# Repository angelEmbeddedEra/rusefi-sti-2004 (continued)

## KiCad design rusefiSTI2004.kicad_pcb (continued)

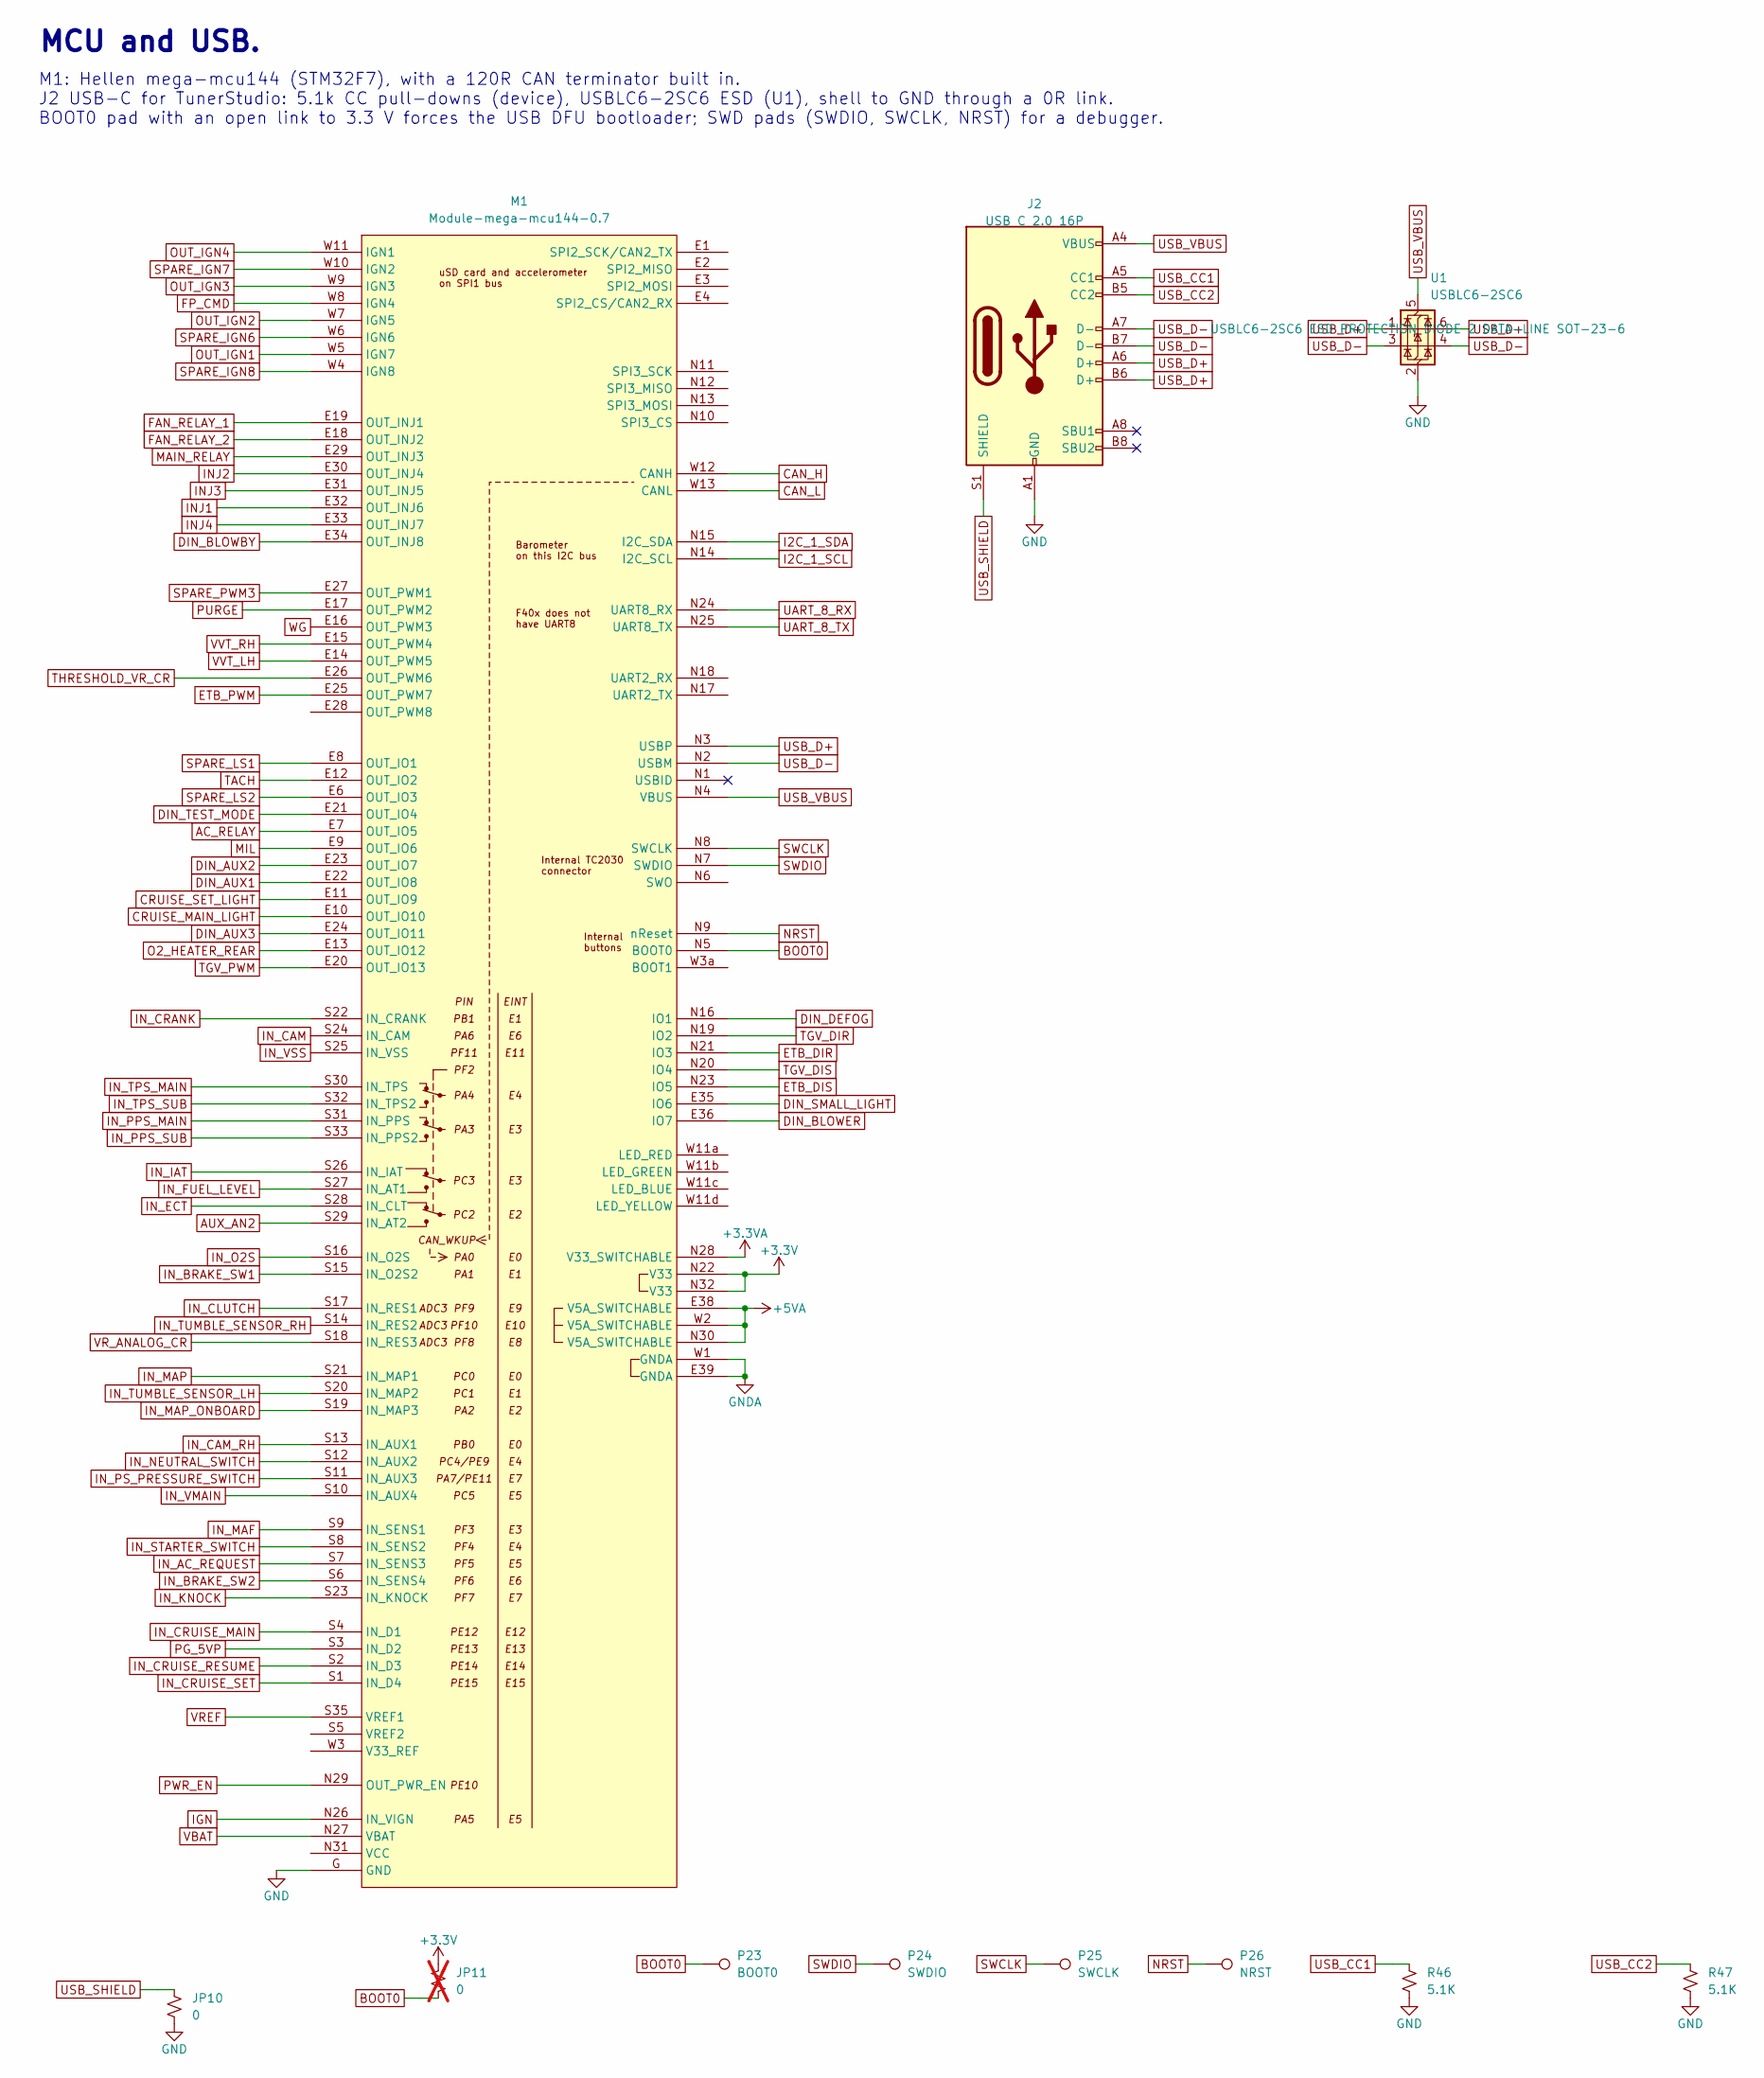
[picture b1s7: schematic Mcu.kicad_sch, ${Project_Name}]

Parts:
J2: USB C 2.0 16P; USB_C_Receptacle_HRO _TYPE-C-31-M-12; LCSC C165948
JP10: 0; R_0805_2012Metric; Manufacturer Part Number RC0805JR-070RL; LCSC C17477
JP11: 0; R_0805_2012Metric; Manufacturer Part Number RC0805JR-070RL; LCSC C17477; not fitted
M1: Module-mega-mcu144-0.7; mega-mcu144
P23: BOOT0; TestPoint_THTPad_D2.0mm_Drill1.0mm
P24: SWDIO; TestPoint_THTPad_D2.0mm_Drill1.0mm
P25: SWCLK; TestPoint_THTPad_D2.0mm_Drill1.0mm
P26: NRST; TestPoint_THTPad_D2.0mm_Drill1.0mm
R46, R47: 5.1K; R_0603_1608Metric; Manufacturer Part Number RC0603FR-075K1L; LCSC C105580
U1: USBLC6-2SC6; SOT-23-6; LCSC C7519

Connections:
+3.3V: JP11.2, M1.N22 (V33), M1.N32 (V33); also elsewhere on the board
+3.3VA: M1.N28 (V33_SWITCHABLE)
+5VA: M1.E38 (V5A_SWITCHABLE), M1.N30 (V5A_SWITCHABLE), M1.W2 (V5A_SWITCHABLE); also elsewhere on the board
AC_RELAY: M1.E7 (OUT_IO5); also elsewhere on the board
AUX_AN2: M1.S29 (IN_AT2); also elsewhere on the board
BOOT0: JP11.1, M1.N5 (BOOT0), P23.1
CAN_H: M1.W12 (CANH); also elsewhere on the board
CAN_L: M1.W13 (CANL); also elsewhere on the board
CRUISE_MAIN_LIGHT: M1.E10 (OUT_IO10); also elsewhere on the board
CRUISE_SET_LIGHT: M1.E11 (OUT_IO9); also elsewhere on the board
DIN_AUX1: M1.E22 (OUT_IO8); also elsewhere on the board
DIN_AUX2: M1.E23 (OUT_IO7); also elsewhere on the board
DIN_AUX3: M1.E24 (OUT_IO11); also elsewhere on the board
DIN_BLOWBY: M1.E34 (OUT_INJ8); also elsewhere on the board
DIN_BLOWER: M1.E36 (IO7); also elsewhere on the board
DIN_DEFOG: M1.N16 (IO1); also elsewhere on the board
DIN_SMALL_LIGHT: M1.E35 (IO6); also elsewhere on the board
DIN_TEST_MODE: M1.E21 (OUT_IO4); also elsewhere on the board
ETB_DIR: M1.N21 (IO3); also elsewhere on the board
ETB_DIS: M1.N23 (IO5); also elsewhere on the board
ETB_PWM: M1.E25 (OUT_PWM7); also elsewhere on the board
FAN_RELAY_1: M1.E19 (OUT_INJ1); also elsewhere on the board
FAN_RELAY_2: M1.E18 (OUT_INJ2); also elsewhere on the board
FP_CMD: M1.W8 (IGN4); also elsewhere on the board
GNDA: M1.E39 (GNDA), M1.W1 (GNDA); also elsewhere on the board
I2C_1_SCL: M1.N14 (I2C_SCL); also elsewhere on the board
I2C_1_SDA: M1.N15 (I2C_SDA); also elsewhere on the board
IGN: M1.N26 (IN_VIGN); also elsewhere on the board
IN_AC_REQUEST: M1.S7 (IN_SENS3); also elsewhere on the board
IN_BRAKE_SW1: M1.S15 (IN_O2S2); also elsewhere on the board
IN_BRAKE_SW2: M1.S6 (IN_SENS4); also elsewhere on the board
IN_CAM: M1.S24 (IN_CAM); also elsewhere on the board
IN_CAM_RH: M1.S13 (IN_AUX1); also elsewhere on the board
IN_CLUTCH: M1.S17 (IN_RES1); also elsewhere on the board
IN_CRANK: M1.S22 (IN_CRANK); also elsewhere on the board
IN_CRUISE_MAIN: M1.S4 (IN_D1); also elsewhere on the board
IN_CRUISE_RESUME: M1.S2 (IN_D3); also elsewhere on the board
IN_CRUISE_SET: M1.S1 (IN_D4); also elsewhere on the board
IN_ECT: M1.S28 (IN_CLT); also elsewhere on the board
IN_FUEL_LEVEL: M1.S27 (IN_AT1); also elsewhere on the board
IN_IAT: M1.S26 (IN_IAT); also elsewhere on the board
IN_KNOCK: M1.S23 (IN_KNOCK); also elsewhere on the board
IN_MAF: M1.S9 (IN_SENS1); also elsewhere on the board
IN_MAP: M1.S21 (IN_MAP1); also elsewhere on the board
IN_MAP_ONBOARD: M1.S19 (IN_MAP3); also elsewhere on the board
IN_NEUTRAL_SWITCH: M1.S12 (IN_AUX2); also elsewhere on the board
IN_O2S: M1.S16 (IN_O2S); also elsewhere on the board
IN_PPS_MAIN: M1.S31 (IN_PPS); also elsewhere on the board
IN_PPS_SUB: M1.S33 (IN_PPS2); also elsewhere on the board
IN_PS_PRESSURE_SWITCH: M1.S11 (IN_AUX3); also elsewhere on the board
IN_STARTER_SWITCH: M1.S8 (IN_SENS2); also elsewhere on the board
IN_TPS_MAIN: M1.S30 (IN_TPS); also elsewhere on the board
IN_TPS_SUB: M1.S32 (IN_TPS2); also elsewhere on the board
IN_TUMBLE_SENSOR_LH: M1.S20 (IN_MAP2); also elsewhere on the board
IN_TUMBLE_SENSOR_RH: M1.S14 (IN_RES2); also elsewhere on the board
IN_VMAIN: M1.S10 (IN_AUX4); also elsewhere on the board
IN_VSS: M1.S25 (IN_VSS); also elsewhere on the board
MAIN_RELAY: M1.E29 (OUT_INJ3); also elsewhere on the board
MIL: M1.E9 (OUT_IO6); also elsewhere on the board
NRST: M1.N9 (nReset), P26.1
OUT_IGN1: M1.W5 (IGN7); also elsewhere on the board
OUT_IGN2: M1.W7 (IGN5); also elsewhere on the board
OUT_IGN3: M1.W9 (IGN3); also elsewhere on the board
OUT_IGN4: M1.W11 (IGN1); also elsewhere on the board
PG_5VP: M1.S3 (IN_D2); also elsewhere on the board
PURGE: M1.E17 (OUT_PWM2); also elsewhere on the board
PWR_EN: M1.N29 (OUT_PWR_EN); also elsewhere on the board
SPARE_IGN6: M1.W6 (IGN6); also elsewhere on the board
SPARE_IGN7: M1.W10 (IGN2); also elsewhere on the board
SPARE_IGN8: M1.W4 (IGN8); also elsewhere on the board
SPARE_LS1: M1.E8 (OUT_IO1); also elsewhere on the board
SPARE_PWM3: M1.E27 (OUT_PWM1); also elsewhere on the board
SWCLK: M1.N8 (SWCLK), P25.1
SWDIO: M1.N7 (SWDIO), P24.1
TACH: M1.E12 (OUT_IO2); also elsewhere on the board
TGV_DIR: M1.N19 (IO2); also elsewhere on the board
TGV_DIS: M1.N20 (IO4); also elsewhere on the board
TGV_PWM: M1.E20 (OUT_IO13); also elsewhere on the board
THRESHOLD_VR_CR: M1.E26 (OUT_PWM6); also elsewhere on the board
UART_8_RX: M1.N24 (UART8_RX); also elsewhere on the board
UART_8_TX: M1.N25 (UART8_TX); also elsewhere on the board
USB_CC1: J2.A5 (CC1), R46.1
USB_CC2: J2.B5 (CC2), R47.1
USB_SHIELD: J2.S1 (SHIELD), JP10.1
VBAT: M1.N27 (VBAT); also elsewhere on the board
VREF: M1.S35 (VREF1); also elsewhere on the board
VR_ANALOG_CR: M1.S18 (IN_RES3); also elsewhere on the board
VVT_LH: M1.E14 (OUT_PWM5); also elsewhere on the board
VVT_RH: M1.E15 (OUT_PWM4); also elsewhere on the board
WG: M1.E16 (OUT_PWM3); also elsewhere on the board

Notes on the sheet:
M1: Hellen mega-mcu144 (STM32F7), with a 120R CAN terminator built in. J2 USB-C for TunerStudio: 5.1k CC pull-downs (device), USBLC6-2SC6 ESD (U1), shell to GND through a 0R link. BOOT0 pad with an open link to 3.3 V forces the USB DFU bootloader; SWD pads (SWDIO, SWCLK, NRST) for a debugger.
MCU and USB.

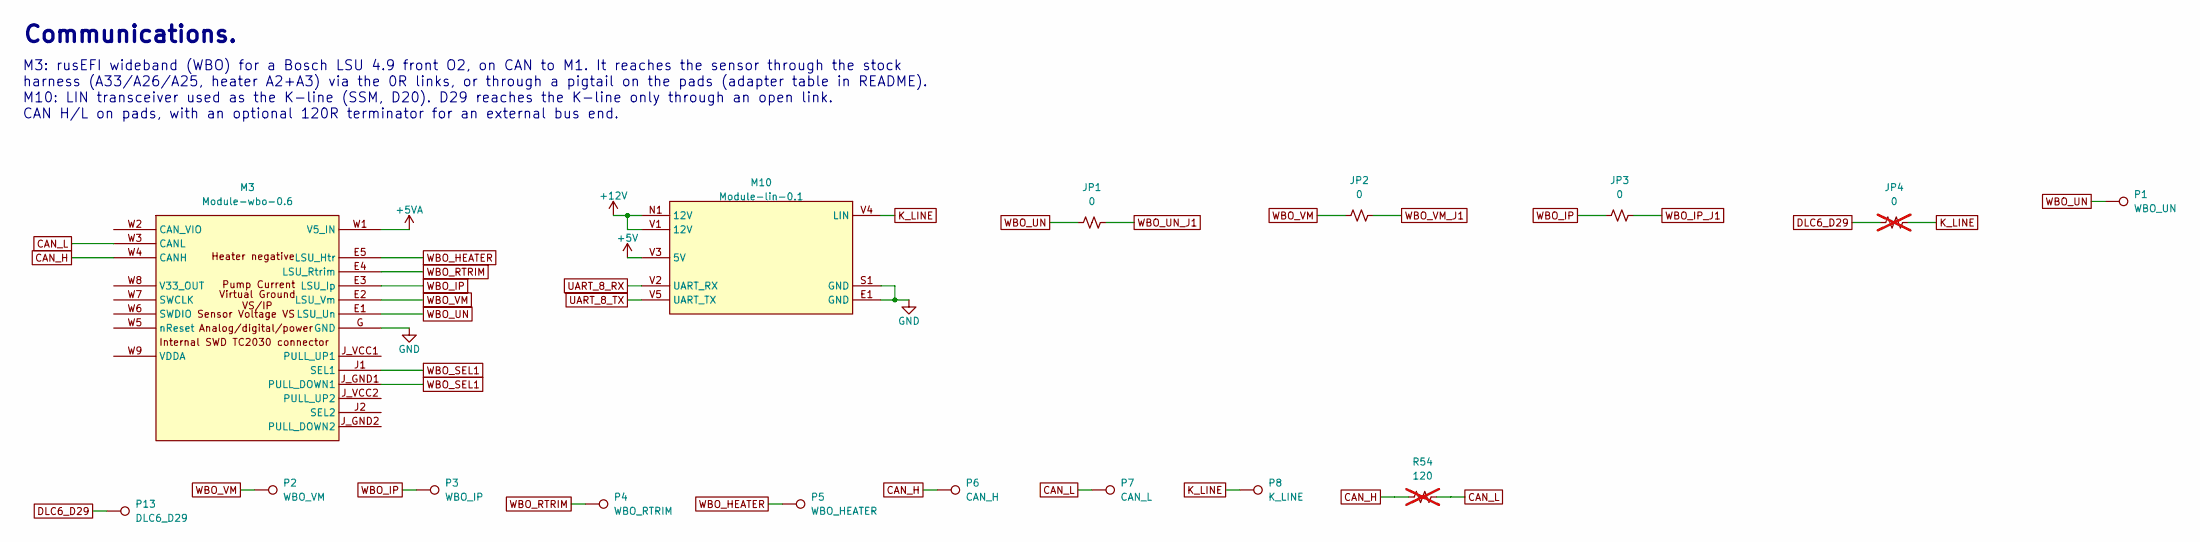
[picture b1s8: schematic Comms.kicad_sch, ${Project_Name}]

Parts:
JP1, JP2, JP3: 0; R_0805_2012Metric; Manufacturer Part Number RC0805JR-070RL; LCSC C17477
JP4: 0; R_0805_2012Metric; Manufacturer Part Number RC0805JR-070RL; LCSC C17477; not fitted
M3: Module-wbo-0.6; wbo
M10: Module-lin-0.1; lin
P1: WBO_UN; TestPoint_THTPad_D2.0mm_Drill1.0mm
P2: WBO_VM; TestPoint_THTPad_D2.0mm_Drill1.0mm
P3: WBO_IP; TestPoint_THTPad_D2.0mm_Drill1.0mm
P4: WBO_RTRIM; TestPoint_THTPad_D2.0mm_Drill1.0mm
P5: WBO_HEATER; TestPoint_THTPad_D2.0mm_Drill1.0mm
P6: CAN_H; TestPoint_THTPad_D2.0mm_Drill1.0mm
P7: CAN_L; TestPoint_THTPad_D2.0mm_Drill1.0mm
P8: K_LINE; TestPoint_THTPad_D2.0mm_Drill1.0mm
P13: DLC6_D29; TestPoint_THTPad_D2.0mm_Drill1.0mm
R54: 120; R_0603_1608Metric; Manufacturer Part Number RC0603FR-07120RL; LCSC C114640; not fitted

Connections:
+5V: M10.V3 (5V); also elsewhere on the board
+5VA: M3.W1 (V5_IN); also elsewhere on the board
+12V: M10.N1 (12V), M10.V1 (12V); also elsewhere on the board
CAN_H: M3.W4 (CANH), P6.1, R54.1; also elsewhere on the board
CAN_L: M3.W3 (CANL), P7.1, R54.2; also elsewhere on the board
DLC6_D29: JP4.1, P13.1; also elsewhere on the board
K_LINE: JP4.2, M10.V4 (LIN), P8.1; also elsewhere on the board
UART_8_RX: M10.V2 (UART_RX); also elsewhere on the board
UART_8_TX: M10.V5 (UART_TX); also elsewhere on the board
WBO_HEATER: M3.E5 (LSU_Htr), P5.1; also elsewhere on the board
WBO_IP: JP3.1, M3.E3 (LSU_Ip), P3.1
WBO_IP_J1: JP3.2; also elsewhere on the board
WBO_RTRIM: M3.E4 (LSU_Rtrim), P4.1
WBO_SEL1: M3.J1 (SEL1), M3.J_GND1 (PULL_DOWN1)
WBO_UN: JP1.1, M3.E1 (LSU_Un), P1.1
WBO_UN_J1: JP1.2; also elsewhere on the board
WBO_VM: JP2.1, M3.E2 (LSU_Vm), P2.1
WBO_VM_J1: JP2.2; also elsewhere on the board

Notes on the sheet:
Communications.
M3: rusEFI wideband (WBO) for a Bosch LSU 4.9 front O2, on CAN to M1. It reaches the sensor through the stock harness (A33/A26/A25, heater A2+A3) via the 0R links, or through a pigtail on the pads (adapter table in README). M10: LIN transceiver used as the K-line (SSM, D20). D29 reaches the K-line 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

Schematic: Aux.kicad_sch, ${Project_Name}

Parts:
F6: nSMD050-24V; Fuse_1206_3216Metric; Manufacturer Part Number nSMD050-24V; LCSC C70076
F7: JK-nSMD005; Fuse_1206_3216Metric; Manufacturer Part Number JK-nSMD005; LCSC C369153
G1: PROTO_AREA; PROTO_AREA_3x5_P2.54mm
H1, H2, H3, H4: MountingHole_3.2mm; MountingHole_3.2mm_M3_DIN965_Pad
J3: Molex_39281143; Molex_Mini-Fit_Jr_5566-14A_2x07_P4.20mm_Vertical; Manufacturer Part Number 39281143
JP7: 0; R_0805_2012Metric; Manufacturer Part Number RC0805JR-070RL; LCSC C17477; not fitted
P11: CHARGE_A22; TestPoint_THTPad_D2.0mm_Drill1.0mm
P14: SPARE_IGN6; TestPoint_THTPad_D2.0mm_Drill1.0mm
P15: SPARE_IGN7; TestPoint_THTPad_D2.0mm_Drill1.0mm
P16: SPARE_IGN8; TestPoint_THTPad_D2.0mm_Drill1.0mm
P17: I2C_1_SCL; TestPoint_THTPad_D2.0mm_Drill1.0mm
P18: I2C_1_SDA; TestPoint_THTPad_D2.0mm_Drill1.0mm
P19: +5VA; TestPoint_THTPad_D2.0mm_Drill1.0mm
P20: +3.3V; TestPoint_THTPad_D2.0mm_Drill1.0mm
P21: +12V_RAW; TestPoint_THTPad_D2.0mm_Drill1.0mm
P22: GND; TestPoint_THTPad_D2.0mm_Drill1.0mm
P27: SPARE_PWM3; TestPoint_THTPad_D2.0mm_Drill1.0mm
P28: MAP_ONBOARD; TestPoint_THTPad_D2.0mm_Drill1.0mm
P29: AUX_IN1; TestPoint_THTPad_D2.0mm_Drill1.0mm
P30: AUX_IN2; TestPoint_THTPad_D2.0mm_Drill1.0mm
P31: AUX_IN3; TestPoint_THTPad_D2.0mm_Drill1.0mm
R48, R49, R50: 4.7K; R_0603_1608Metric; Manufacturer Part Number RC0603FR-074K7L; LCSC C99782; not fitted

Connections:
+3.3V: P20.1; also elsewhere on the board
+5VA: P19.1; also elsewhere on the board
+5VAS: F7.1; also elsewhere on the board
+12V_RAW: F6.1, P21.1; also elsewhere on the board
AUX_5V: F7.2, J3.3
AUX_12V: F6.2, J3.1
AUX_AN2: J3.9, JP7.2; also elsewhere on the board
AUX_IN1: J3.5, P29.1, R48.1; also elsewhere on the board
AUX_IN2: J3.6, P30.1, R49.1; also elsewhere on the board
AUX_IN3: J3.7, P31.1, R50.1; also elsewhere on the board
CAN_H: J3.12; also elsewhere on the board
CAN_L: J3.13; also elsewhere on the board
CHARGE_A22: P11.1; also elsewhere on the board
FP_STATUS: JP7.1; also elsewhere on the board
GND_SENSOR: J3.4; also elsewhere on the board
I2C_1_SCL: P17.1; also elsewhere on the board
I2C_1_SDA: P18.1; also elsewhere on the board
IN_MAP_ONBOARD: P28.1; also elsewhere on the board
OUT_SPARE_LS1: J3.10; also elsewhere on the board
OUT_SPARE_LS2: J3.11; also elsewhere on the board
SPARE_IGN6: P14.1; also elsewhere on the board
SPARE_IGN7: P15.1; also elsewhere on the board
SPARE_IGN8: P16.1; also elsewhere on the board
SPARE_PWM3: P27.1; also elsewhere on the board

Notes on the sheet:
Aux connector and expansion.
J3: Molex Mini-Fit Jr 2x7 (pinout in documents/README.md): fused 12 V and 5 V, sensor ground, three digital inputs, two analog inputs, two low-side outputs, CAN. Spare MCU pins (IGN6-8, I2C, OUT_PWM3, IN_RES2) and every rail are on pads next to the prototype area G1.
Mounting: H1-H4 M3 plated holes, no net (the board is not grounded to the case through them). J1's three screws hold the connector to the board only.

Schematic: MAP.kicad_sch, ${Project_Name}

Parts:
C1: 100n_50V_X7R; C_0603_1608Metric; Manufacturer Part Number CC0603KRX7R9BB104
U20: MPXH6400A; PRESSURE_8-SSOP; Manufacturer Part Number MPXHZ6400AC6T1; LCSC C511770

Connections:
+5VA: C1.1, U20.2 (Vcc); also elsewhere on the board
IN_MAP_ONBOARD: U20.4 (Vout); also elsewhere on the board

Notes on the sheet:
On-board MAP sensor, as rusEFI AlphaX-4chan (MAP.kicad_sch): NXP MPXHZ6400AC6T1, 20-400 kPa absolute, 5 V from +5VA, 100 nF at Vs, Vout straight to M1 IN_MAP3 (S19). The M1 input has its own divider and filter. Firmware: map.sensor.hwChannel = H144_IN_MAP3, type MT_MPXH6400. Run a hose from the por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

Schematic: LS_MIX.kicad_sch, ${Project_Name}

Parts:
Q4: NCV8401BDTRKG; TO-252-2; Manufacturer Part Number NCV8401BDTRKG
R3, R4, R5, R6: 4.7K; R_0603_1608Metric; Manufacturer Part Number RC0603FR-074K7L; LCSC C99782
U1, U2: VNLD5160TR-E; SOIC-8_3.9x4.9mm_P1.27mm; Manufacturer Part Number VNLD5160TR-E; LCSC C377942

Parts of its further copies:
Q16: NCV8401BDTRKG; TO-252-2; Manufacturer Part Number NCV8401BDTRKG
R7, R8, R9, R10, R11, R12, R13, R14, R15, R16, R17, R18, R19, R20, R21, R22: 4.7K; R_0603_1608Metric; Manufacturer Part Number RC0603FR-074K7L; LCSC C99782
U10, U11, U12, U13, U14, U15, U16, U17, U18, U19: VNLD5160TR-E; SOIC-8_3.9x4.9mm_P1.27mm; Manufacturer Part Number VNLD5160TR-E; LCSC C377942

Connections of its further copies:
AC_RELAY: R15.1, U18.1 (IN); also elsewhere on the board
CRUISE_MAIN_LIGHT: R19.1, U16.1 (IN); also elsewhere on the board
CRUISE_SET_LIGHT: R20.1, U16.3 (IN); also elsewhere on the board
ELECTRONIC_THROTTE_RELAY: R10.1, U13.3 (IN)
FAN_RELAY_1: R8.1, U12.3 (IN); also elsewhere on the board
FAN_RELAY_2: R9.1, U13.1 (IN); also elsewhere on the board
MAIN_RELAY: R7.1, U12.1 (IN); also elsewhere on the board
MIL: R21.1, U17.1 (IN); also elsewhere on the board
OUT_AC_RELAY: U18.8 (D); also elsewhere on the board
OUT_CRUISE_MAIN_LIGHT: U16.8 (D); also elsewhere on the board
OUT_CRUISE_SET_LIGHT: U16.6 (D); also elsewhere on the board
OUT_ELECTRONIC_THROTTE_RELAY: U13.6 (D); also elsewhere on the board
OUT_FAN_RELAY_1: U12.6 (D); also elsewhere on the board
OUT_FAN_RELAY_2: U13.8 (D); also elsewhere on the board
OUT_INJ1: U10.8 (D); also elsewhere on the board
OUT_INJ2: U10.6 (D); also elsewhere on the board
OUT_INJ3: U11.8 (D); also elsewhere on the board
OUT_INJ4: U11.6 (D); also elsewhere on the board
OUT_MAIN_RELAY: U12.8 (D); also elsewhere on the board
OUT_MIL: U17.8 (D); also elsewhere on the board
OUT_O2_HEATER_REAR: Q16.2 (D); also elsewhere on the board
OUT_PURGE_CONTROL: U15.6 (D); also elsewhere on the board
OUT_SPARE_LS1: U18.6 (D); also elsewhere on the board
OUT_SPARE_LS2: U19.8 (D); also elsewhere on the board
OUT_TACH: U17.6 (D); also elsewhere on the board
OUT_VVT_LH-: U15.8 (D); also elsewhere on the board
OUT_VVT_RH-: U14.6 (D); also elsewhere on the board
OUT_WG: U14.8 (D); also elsewhere on the board
PURGE: R14.1, U15.3 (IN); also elsewhere on the board
SPARE_LS1: R16.1, U18.3 (IN); also elsewhere on the board
TACH: R22.1, U17.3 (IN); also elsewhere on the board
VVT_LH: R13.1, U15.1 (IN); also elsewhere on the board
VVT_RH: R12.1, U14.3 (IN); also elsewhere on the board
WG: R11.1, U14.1 (IN); also elsewhere on the board

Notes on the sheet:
U19 channel 2: unused spare (input and drain open, as the datasheet allows).

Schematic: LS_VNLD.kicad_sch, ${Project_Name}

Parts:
R3, R4, R5, R6: 4.7K; R_0603_1608Metric; Manufacturer Part Number RC0603FR-074K7L; LCSC C99782
U1, U2: VNLD5160TR-E; SOIC-8_3.9x4.9mm_P1.27mm; Manufacturer Part Number VNLD5160TR-E; LCSC C377942

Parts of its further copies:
R7, R8, R9, R10, R11, R12, R13, R14, R15, R16, R17, R18, R19, R20, R21, R22: 4.7K; R_0603_1608Metric; Manufacturer Part Number RC0603FR-074K7L; LCSC C99782
U10, U11, U12, U13, U14, U15, U16, U17, U18, U19: VNLD5160TR-E; SOIC-8_3.9x4.9mm_P1.27mm; Manufacturer Part Number VNLD5160TR-E; LCSC C377942

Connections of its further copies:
AC_RELAY: R15.1, U18.1 (IN); also elsewhere on the board
CRUISE_MAIN_LIGHT: R19.1, U16.1 (IN); also elsewhere on the board
CRUISE_SET_LIGHT: R20.1, U16.3 (IN); also elsewhere on the board
ELECTRONIC_THROTTE_RELAY: R10.1, U13.3 (IN)
FAN_RELAY_1: R8.1, U12.3 (IN); also elsewhere on the board
FAN_RELAY_2: R9.1, U13.1 (IN); also elsewhere on the board
MAIN_RELAY: R7.1, U12.1 (IN); also elsewhere on the board
MIL: R21.1, U17.1 (IN); also elsewhere on the board
OUT_AC_RELAY: U18.8 (D); also elsewhere on the board
OUT_CRUISE_MAIN_LIGHT: U16.8 (D); also elsewhere on the board
OUT_CRUISE_SET_LIGHT: U16.6 (D); also elsewhere on the board
OUT_ELECTRONIC_THROTTE_RELAY: U13.6 (D); also elsewhere on the board
OUT_FAN_RELAY_1: U12.6 (D); also elsewhere on the board
OUT_FAN_RELAY_2: U13.8 (D); also elsewhere on the board
OUT_INJ1: U10.8 (D); also elsewhere on the board
OUT_INJ2: U10.6 (D); also elsewhere on the board
OUT_INJ3: U11.8 (D); also elsewhere on the board
OUT_INJ4: U11.6 (D); also elsewhere on the board
OUT_MAIN_RELAY: U12.8 (D); also elsewhere on the board
OUT_MIL: U17.8 (D); also elsewhere on the board
OUT_PURGE_CONTROL: U15.6 (D); also elsewhere on the board
OUT_SPARE_LS1: U18.6 (D); also elsewhere on the board
OUT_SPARE_LS2: U19.8 (D); also elsewhere on the board
OUT_TACH: U17.6 (D); also elsewhere on the board
OUT_VVT_LH-: U15.8 (D); also elsewhere on the board
OUT_VVT_RH-: U14.6 (D); also elsewhere on the board
OUT_WG: U14.8 (D); also elsewhere on the board
PURGE: R14.1, U15.3 (IN); also elsewhere on the board
SPARE_LS1: R16.1, U18.3 (IN); also elsewhere on the board
TACH: R22.1, U17.3 (IN); also elsewhere on the board
VVT_LH: R13.1, U15.1 (IN); also elsewhere on the board
VVT_RH: R12.1, U14.3 (IN); also elsewhere on the board
WG: R11.1, U14.1 (IN); also elsewhere on the board

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
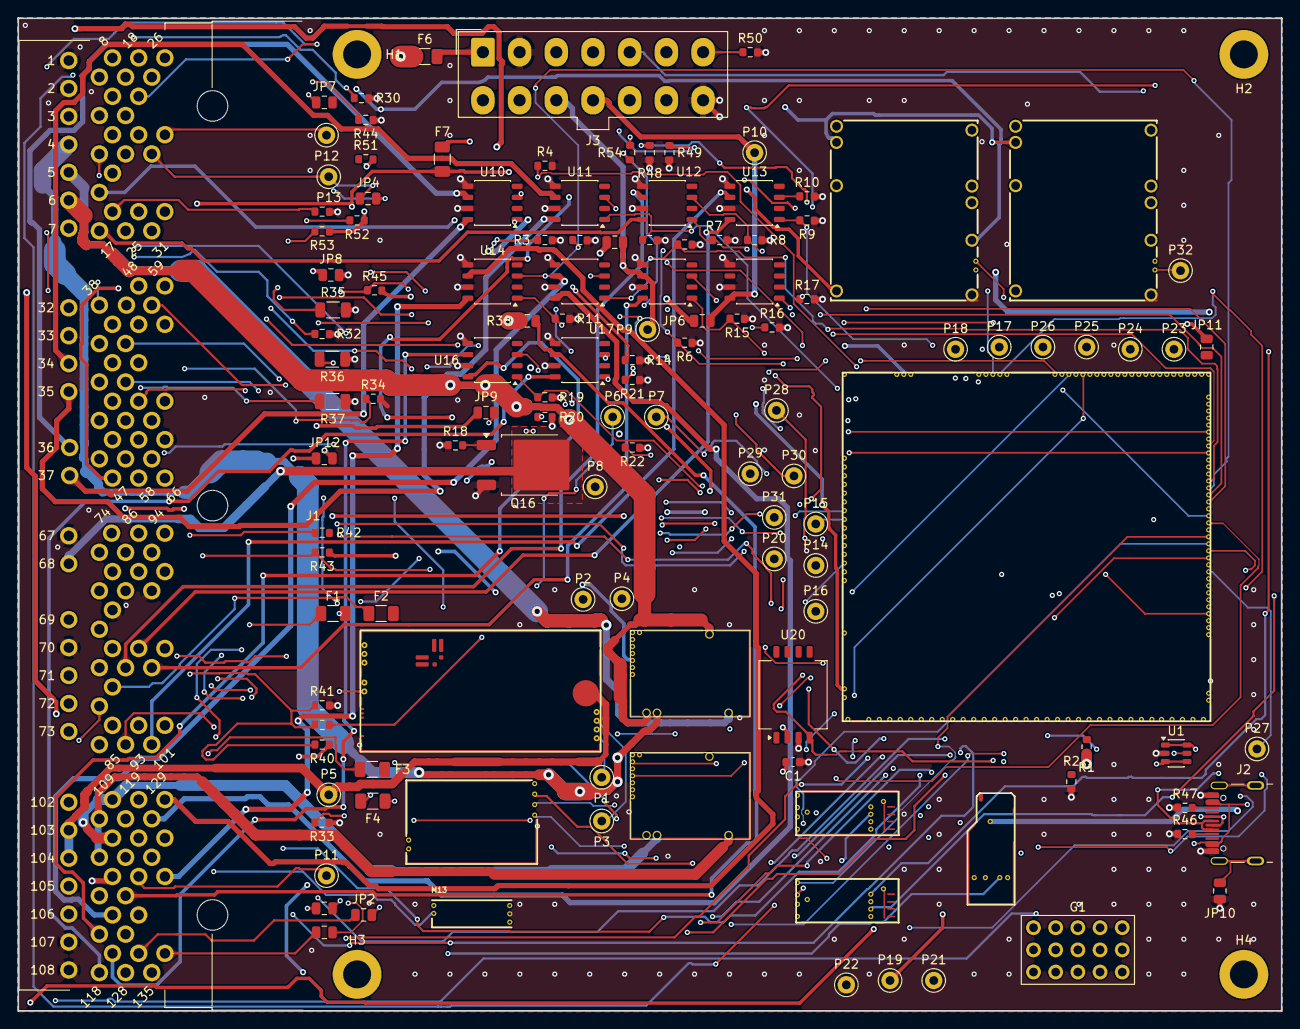
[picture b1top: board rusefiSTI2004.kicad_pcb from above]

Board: 6 copper layers, 144.6 x 113.6 mm, 130 parts (0 on the bottom side), 167 nets.

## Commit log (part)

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2025-02-17 test
    added a few modules
2025-02-19 IGN,INJ AND ETB WIRED
    wip WORKED ON IGNITION AND INJECTORS,etb
2025-02-19 started laying it out
    quick layout
2025-02-19 test2
    added silk
2025-02-19 test3
    silk3
2025-02-19 [skip actions] Auto-generated board v2.1
2025-02-19 test4
    test
2025-03-11 GHA says update hellen-one
2025-03-13 GHA says update kicad6-libraries
